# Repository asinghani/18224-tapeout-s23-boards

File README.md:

# 18-224 S23 Tapeout Bringup

## Getting Started

If you have picked up your kit from ECE, please see [BRINGUP.md](docs/BRINGUP.md) for instructions on how to get started using it!

If you are interested in the process to assemble the boards/kits, see [ASSEMBLY.md](docs/ASSEMBLY.md)

## Schematics

- Breakout Board v1 [Schematic](pcb/breakout_board_v1/schematic.pdf)
- Buttons/Switches Board [Schematic](pcb/manual_gpio_board/schematic.pdf)
- Debugger Board [Schematic](pcb/debugger_board_v1/schematic.pdf)

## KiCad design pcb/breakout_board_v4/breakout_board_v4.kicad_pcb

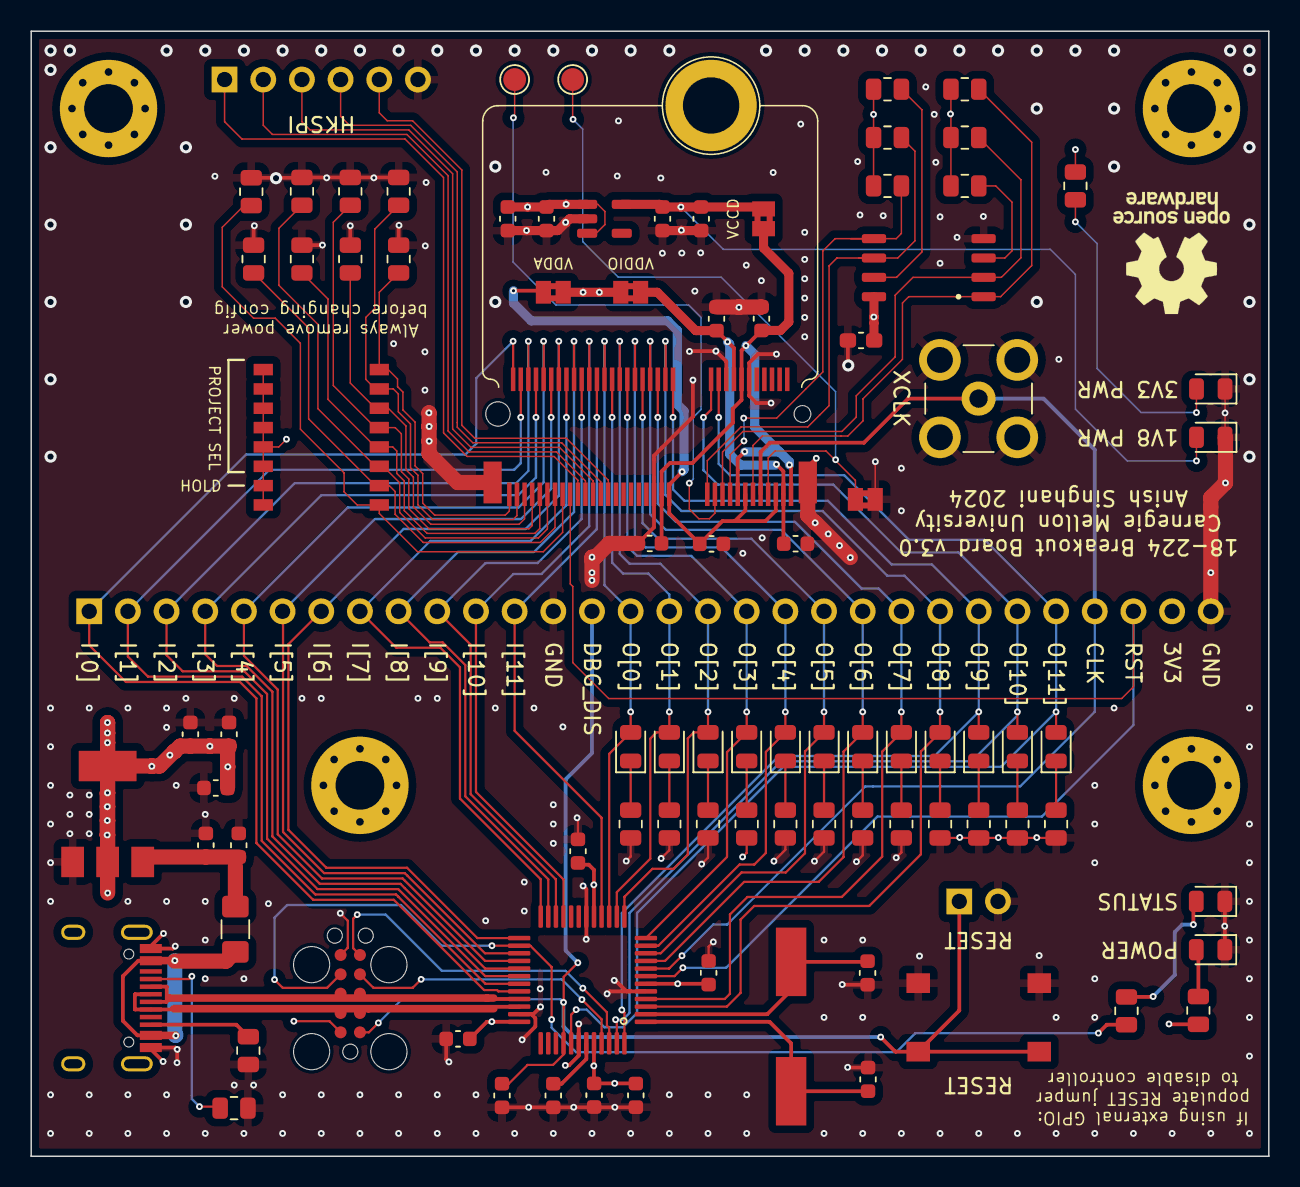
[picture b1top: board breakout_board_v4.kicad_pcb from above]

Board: 4 copper layers, 81.3 x 73.9 mm, 97 parts (0 on the bottom side), 81 nets.

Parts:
C1, C2: 22p; C_0603_1608Metric
C3, C5, C7, C8, C9, C12, C13, C20: 0.1u; C_0603_1608Metric
C4, C6, C11, C14, C15, C19, C21, C24: 1u; C_0603_1608Metric
C10, C16, C18, C22, C23: 10u; C_0603_1608Metric
C17: DNF; C_0603_1608Metric_Pad1.08x0.95mm_HandSolder
D1: 3V3; LED_0805_2012Metric
D2, D3, D4, D6, D7, D8, D9, D10, D11, D12, D13, D14, D15, D16: LED; LED_0805_2012Metric
D5: 1V8; LED_0805_2012Metric
F1: 500mA; Fuse_1206_3216Metric_Pad1.42x1.75mm_HandSolder
H1: MICROMOD-Standoff; MicroMod-Standoff
H2, H3, H4, H5: MountingHole; MountingHole_3.2mm_M3_Pad_Via
J1: TC2050; Tag-Connect_TC2050-IDC-FP_2x05_P1.27mm_Vertical
J2: SMA_CONN; SMB_Jack_Vertical
J3: BREAKOUT_HDR; PinHeader_1x30_P2.54mm_Vertical
J4: HKSPI_HDR; PinHeader_1x06_P2.54mm_Vertical
J5: USB_C_Receptacle_USB2.0; USB_C_Receptacle_HRO_TYPE-C-31-M-12
JP1: RST_JMP; PinHeader_1x02_P2.54mm_Vertical
JP2: VCCD_JMP; SolderJumper-2_P1.3mm_Bridged2Bar_Pad1.0x1.5mm
JP3: VDDA_JMP; SolderJumper-2_P1.3mm_Bridged2Bar_Pad1.0x1.5mm
JP4: SOC_RST_JMP; SolderJumper-2_P1.3mm_Bridged2Bar_Pad1.0x1.5mm
JP5: VDDIO_JMP; SolderJumper-2_P1.3mm_Bridged2Bar_Pad1.0x1.5mm
R1, R2, R3, R4, R5, R6, R7, R8, R12: 10K; R_0805_2012Metric
R9, R10, R11, R13, R14: DNF; R_0805_2012Metric
R15, R16, R17, R18, R19, R20, R21, R22, R23, R24, R25, R26, R27, R28, R29: 1K; R_0805_2012Metric
R30, R31: 5.1K; R_0805_2012Metric
SW1: RST_BTN; SW_Push_1P1T_NO_6x6mm_H9.5mm
SW2: DSHP08TSGER; SW_DIP_SPSTx08_Slide_KingTek_DSHP08TS_W7.62mm_P1.27mm
TP1: CARAVEL_GPIO_TP; TestPoint_Pad_D1.5mm
TP2: RST_TP; TestPoint_Pad_D1.5mm
U1: ATSAMD21G18A-A; TQFP-48_7x7mm_P0.5mm
U2: caravel-M.2-card; M.2-CONNECTOR-E
U3: AP2112K-1.8; SOT-23-5
U4: DNF; SOIC-8_5.23x5.23mm_P1.27mm
U5: AZ1117-3.3; SOT-223-3_TabPin2
Y1: 32.768KHz; Crystal_SMD_HC49-SD

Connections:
+1V8: C14.1, C16.1, D5.2 (A), JP2.2 (B), U3.5 (VOUT)
+3V3: C4.1, C5.1, C7.1, C8.1, C9.1, C10.1, C12.1, C17.1, C22.1, C23.1, C24.1, J1.10, J3.29, JP3.2 (B), JP5.2 (B), R9.1, R10.1, R11.1, R12.1, R13.1, R14.1, R15.2, R21.1, SW2.1, SW2.2, SW2.3, SW2.4, SW2.5, SW2.6, SW2.7, SW2.8, U1.6 (VDDANA), U1.17 (VDDIO), U1.36 (VDDIO), U1.44 (VDDIN), U3.1 (VIN), U3.3 (EN), U4.8 (VCC), U5.2 (VO)
+5V: C18.1, C21.1, F1.1, U5.3 (VI)
Caravel_CSB: R9.2, U2.11 (Caravel_CSB), U4.1 (~CS)
Caravel_D0: R11.2, U2.17 (Caravel_D0), U4.5 (DI(IO0))
Caravel_D1: R12.2, U2.19 (Caravel_D1), U4.2 (DO(IO1))
Caravel_SCK: R10.2, U2.23 (Caravel_SCK), U4.6 (CLK)
Flash_HOLD: R14.2, U4.7 (IO3)
Flash_WP: R13.2, U4.3 (IO2)
GND: C1.1, C2.1, C3.2, C4.2, C5.2, C6.1, C7.2, C8.2, C9.2, C10.2, C11.2, C12.2, C13.2, C14.2, C15.2, C16.2, C17.2, C18.2, C19.2, C20.2, C21.2, C22.2, C23.2, C24.2, D1.1 (K), D4.1 (K), D5.1 (K), D8.1 (K), J1.6, J2.2 (Ext), J3.13, J3.30, J4.6, J5.A1 (GND), J5.A12 (GND), J5.B1 (GND), J5.B12 (GND), JP1.2 (B), JP4.2 (B), R1.2, R2.2, R3.2, R4.2, R5.2, R6.2, R7.2, R8.2, R16.2, R17.2, R19.2, R20.2, R22.2, R23.2, R24.2, R25.2, R26.2, R27.2, R28.2, R29.2, R30.1, R31.1, SW1.1, U1.5 (GNDANA), U1.18 (GND), U1.35 (GND), U1.42 (GND), U2.12 (GND), U2.18 (GND), U2.37 (GND), U2.A1 (GND), U2.A2 (GND), U3.2 (GND), U4.4 (GND), U5.1 (GND)
unnamed: D1.2 (A), R15.1
unnamed: D2.1 (K), R16.1
unnamed: D3.1 (K), R17.1
unnamed: D4.2 (A), R18.2
unnamed: D6.1 (K), R19.1
unnamed: D7.1 (K), R20.1
unnamed: D8.2 (A), R21.2
unnamed: D9.1 (K), R22.1
unnamed: D10.1 (K), R23.1
unnamed: D11.1 (K), R24.1
unnamed: D12.1 (K), R25.1
unnamed: D13.1 (K), R26.1
unnamed: D14.1 (K), R27.1
unnamed: D15.1 (K), R28.1
unnamed: D16.1 (K), R29.1
unnamed: F1.2, J5.A4 (VBUS), J5.A9 (VBUS), J5.B4 (VBUS), J5.B9 (VBUS)
unnamed: J5.A5 (CC1), R30.2
unnamed: J5.B5 (CC2), R31.2
unnamed: C1.2, U1.1 (PA00), Y1.1
unnamed: C2.2, U1.2 (PA01), Y1.2
unnamed: C6.2, U1.43 (VDDCORE)
RESETn: C3.1, J1.1, J3.14, JP1.1 (A), SW1.2, U1.40 (~RESET)
SWC: J1.4, U1.45 (PA30)
SWD: J1.5, U1.46 (PA31)
USB_DM: J1.3, J1.8, J5.A7 (D-), J5.B7 (D-), U1.33 (PA24)
USB_DP: J1.2, J1.9, J5.A6 (D+), J5.B6 (D+), U1.34 (PA25)
gpio: TP1.1, U2.21 (gpio)
in0: J3.1, U1.32 (PA23), U2.74 (mprj_io[14])
in1: J3.2, U1.31 (PA22), U2.72 (mprj_io[15])
in2: J3.3, U1.30 (PA21), U2.70 (mprj_io[16])
in3: J3.4, U1.29 (PA20), U2.68 (mprj_io[17])
in4: J3.5, U1.28 (PA19), U2.66 (mprj_io[18])
in5: J3.6, U1.27 (PA18), U2.64 (mprj_io[19])
in6: J3.7, U1.25 (PA16), U2.62 (mprj_io[20])
in7: J3.8, U1.24 (PA15), U2.60 (mprj_io[21])
in8: J3.9, U1.23 (PA14), U2.58 (mprj_io[22])
in9: J3.10, U1.22 (PA13), U2.56 (mprj_io[23])
in10: J3.11, U1.21 (PA12), U2.54 (mprj_io[24])
in11: J3.12, U1.16 (PA11), U2.52 (mprj_io[25])
mprj_io[0]: J4.5, U2.49 (mprj_io[0])
mprj_io[1]_SDO: J4.4, U2.51 (mprj_io[1]_SDO)
mprj_io[2]_SDI: J4.3, U2.53 (mprj_io[2]_SDI)
mprj_io[3]_CSB: J4.2, U2.55 (mprj_io[3]_CSB)
mprj_io[4]_SCK: J4.1, U2.57 (mprj_io[4]_SCK)
mprj_io[5]_ser_rx: J3.28, U1.7 (PB08), U2.59 (mprj_io[5]_ser_rx)
mprj_io[6]_ser_tx: R1.1, SW2.9, U2.61 (mprj_io[6]_ser_tx)
mprj_io[7]: R2.1, SW2.10, U2.63 (mprj_io[7])
mprj_io[8]: R3.1, SW2.11, U2.65 (mprj_io[8])
mprj_io[9]: R4.1, SW2.12, U2.67 (mprj_io[9])
mprj_io[10]: R5.1, SW2.13, U2.69 (mprj_io[10])
mprj_io[11]: R6.1, SW2.14, U2.71 (mprj_io[11])
mprj_io[12]: R7.1, SW2.15, U2.73 (mprj_io[12])
mprj_io[13]: R8.1, SW2.16, U2.75 (mprj_io[13])
mprj_io[26]: D2.2 (A), J3.15, U1.15 (PA10), U2.50 (mprj_io[26])
mprj_io[27]: D6.2 (A), J3.16, U1.14 (PA09), U2.48 (mprj_io[27])
mprj_io[28]: D9.2 (A), J3.17, U1.13 (PA08), U2.46 (mprj_io[28])
mprj_io[29]: D11.2 (A), J3.18, U1.12 (PA07), U2.44 (mprj_io[29])
mprj_io[30]: D13.2 (A), J3.19, U1.11 (PA06), U2.42 (mprj_io[30])
mprj_io[31]: D15.2 (A), J3.20, U1.10 (PA05), U2.40 (mprj_io[31])
mprj_io[32]: D3.2 (A), J3.21, U1.9 (PA04), U2.38 (mprj_io[32])
mprj_io[33]: D7.2 (A), J3.22, U1.4 (PA03), U2.36 (mprj_io[33])
mprj_io[34]: D10.2 (A), J3.23, U1.3 (PA02), U2.34 (mprj_io[34])
mprj_io[35]: D12.2 (A), J3.24, U1.48 (PB03), U2.32 (mprj_io[35])
mprj_io[36]: D14.2 (A), J3.25, U1.47 (PB02), U2.22 (mprj_io[36])
mprj_io[37]: D16.2 (A), J3.26, U1.41 (PA28), U2.20 (mprj_io[37])
status: J1.7, R18.1, U1.26 (PA17)
uio_clk: J2.1 (In), J3.27, U1.8 (PB09), U2.9 (xclk)
vccd: C11.1, C13.1, JP2.1 (A), U2.1 (vccd2), U2.14 (vccd), U2.15 (vcdd), U2.35 (vccd1)
vdda: C15.1, JP3.1 (A), U2.5 (vdda), U2.13 (vdda2), U2.33 (vdda1)
vddio: C19.1, C20.1, JP5.1 (A), U2.3 (vddio), U2.16 (vddio)
~RST: JP4.1 (A), TP2.1, U2.7 (~RST)

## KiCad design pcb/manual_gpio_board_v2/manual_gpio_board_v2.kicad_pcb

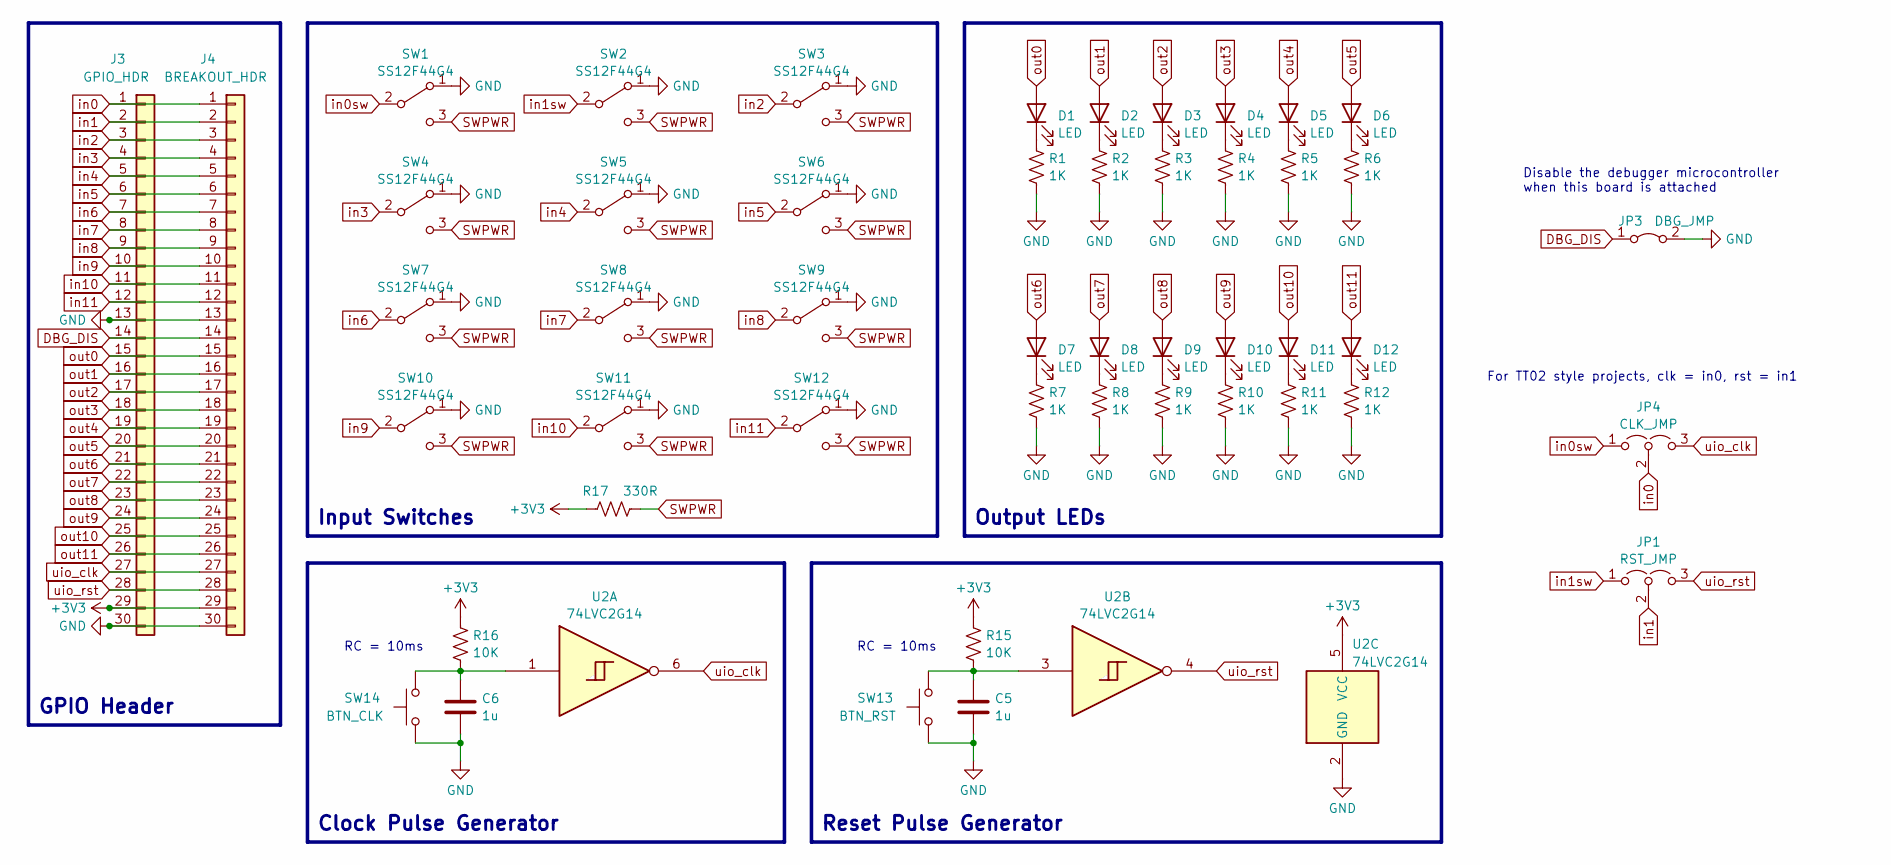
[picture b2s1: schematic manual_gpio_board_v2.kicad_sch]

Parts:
C5, C6: 1u; C_0603_1608Metric; LCSC C15849
D1, D2, D3, D4, D5, D6, D7, D8, D9, D10, D11, D12: LED; LED_0805_2012Metric; LCSC C98221
J3: GPIO_HDR; PinHeader_1x30_P2.54mm_Vertical
J4: BREAKOUT_HDR; PinHeader_1x30_P2.54mm_Vertical
JP1: RST_JMP; PinHeader_1x03_P2.54mm_Vertical
JP3: DBG_JMP; SolderJumper-2_P1.3mm_Bridged_Pad1.0x1.5mm
JP4: CLK_JMP; PinHeader_1x03_P2.54mm_Vertical
R1, R2, R3, R4, R5, R6, R7, R8, R9, R10, R11, R12: 1K; R_0805_2012Metric; LCSC C17513
R15, R16: 10K; R_0805_2012Metric; LCSC C17414
R17: 330R; R_0805_2012Metric; LCSC C17630
SW1, SW2, SW3, SW4, SW5, SW6, SW7, SW8, SW9, SW10, SW11, SW12: SS12F44G4
SW13: BTN_RST; SW_Push_1P1T_NO_6x6mm_H9.5mm; LCSC C294566
SW14: BTN_CLK; SW_Push_1P1T_NO_6x6mm_H9.5mm; LCSC C294566
U2: 74LVC2G14; SOT-23-6; LCSC C12401

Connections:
+3V3: J3.29, R15.1, R16.1, R17.1, U2.5 (VCC); also elsewhere on the board
DBG_DIS: J3.14, JP3.1 (A); also elsewhere on the board
GND: C5.2, C6.2, J3.13, J3.30, JP3.2 (B), R1.2, R2.2, R3.2, R4.2, R5.2, R6.2, R7.2, R8.2, R9.2, R10.2, R11.2, R12.2, SW1.1 (A), SW2.1 (A), SW3.1 (A), SW4.1 (A), SW5.1 (A), SW6.1 (A), SW7.1 (A), SW8.1 (A), SW9.1 (A), SW10.1 (A), SW11.1 (A), SW12.1 (A), SW13.1, SW14.1, U2.2 (GND); also elsewhere on the board
unnamed: C5.1, R15.2, SW13.2, U2.3
unnamed: C6.1, R16.2, SW14.2, U2.1
unnamed: D1.1 (K), R1.1
unnamed: D2.1 (K), R2.1
unnamed: D3.1 (K), R3.1
unnamed: D4.1 (K), R4.1
unnamed: D5.1 (K), R5.1
unnamed: D6.1 (K), R6.1
unnamed: D7.1 (K), R7.1
unnamed: D8.1 (K), R8.1
unnamed: D9.1 (K), R9.1
unnamed: D10.1 (K), R10.1
unnamed: D11.1 (K), R11.1
unnamed: D12.1 (K), R12.1
SWPWR: R17.2, SW1.3 (C), SW2.3 (C), SW3.3 (C), SW4.3 (C), SW5.3 (C), SW6.3 (C), SW7.3 (C), SW8.3 (C), SW9.3 (C), SW10.3 (C), SW11.3 (C), SW12.3 (C)
in0: J3.1, JP4.2 (C); also elsewhere on the board
in0sw: JP4.1 (A), SW1.2 (B)
in1: J3.2, JP1.2 (C); also elsewhere on the board
in1sw: JP1.1 (A), SW2.2 (B)
in2: J3.3, SW3.2 (B); also elsewhere on the board
in3: J3.4, SW4.2 (B); also elsewhere on the board
in4: J3.5, SW5.2 (B); also elsewhere on the board
in5: J3.6, SW6.2 (B); also elsewhere on the board
in6: J3.7, SW7.2 (B); also elsewhere on the board
in7: J3.8, SW8.2 (B); also elsewhere on the board
in8: J3.9, SW9.2 (B); also elsewhere on the board
in9: J3.10, SW10.2 (B); also elsewhere on the board
in10: J3.11, SW11.2 (B); also elsewhere on the board
in11: J3.12, SW12.2 (B); also elsewhere on the board
out0: D1.2 (A), J3.15; also elsewhere on the board
out1: D2.2 (A), J3.16; also elsewhere on the board
out2: D3.2 (A), J3.17; also elsewhere on the board
out3: D4.2 (A), J3.18; also elsewhere on the board
out4: D5.2 (A), J3.19; also elsewhere on the board
out5: D6.2 (A), J3.20; also elsewhere on the board
out6: D7.2 (A), J3.21; also elsewhere on the board
out7: D8.2 (A), J3.22; also elsewhere on the board
out8: D9.2 (A), J3.23; also elsewhere on the board
out9: D10.2 (A), J3.24; also elsewhere on the board
out10: D11.2 (A), J3.25; also elsewhere on the board
out11: D12.2 (A), J3.26; also elsewhere on the board
uio_clk: J3.27, JP4.3 (B), U2.6; also elsewhere on the board
uio_rst: J3.28, JP1.3 (B), U2.4; also elsewhere on the board

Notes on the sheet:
For TT02 style projects, clk = in0, rst = in1
RC = 10ms
Disable the debugger microcontroller when this board is attached
Input Switches
Reset Pulse Generator
Clock Pulse Generator
GPIO Header
Output LEDs

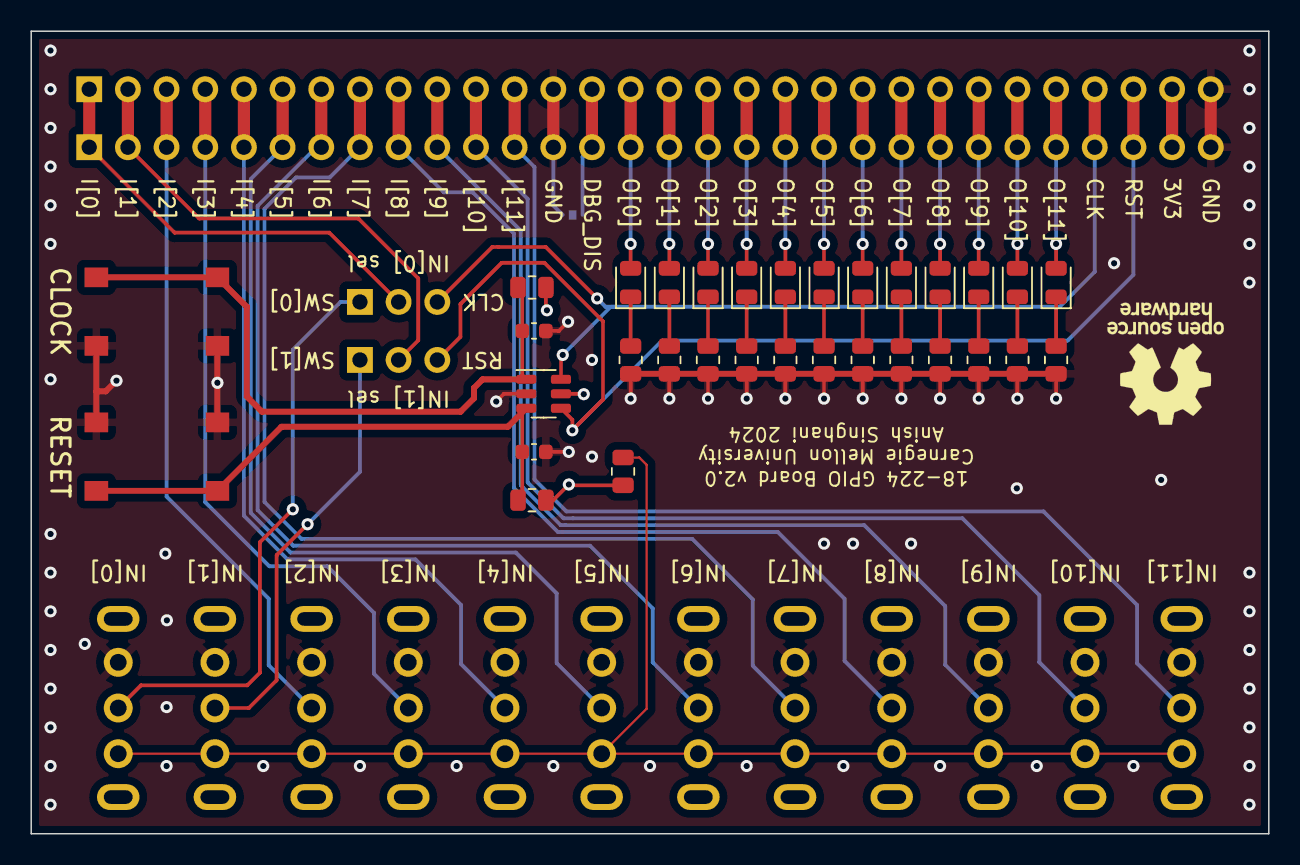
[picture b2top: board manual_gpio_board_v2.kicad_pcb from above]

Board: 4 copper layers, 81.3 x 52.7 mm, 49 parts (1 on the bottom side), 46 nets.

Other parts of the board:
J1: GPIO_HDR; PinHeader_1x30_P2.54mm_Vertical

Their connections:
+3V3: J1.29; also elsewhere on the board
DBG_DIS: J1.14; also elsewhere on the board
GND: J1.13, J1.30; also elsewhere on the board
in0: J1.1; also elsewhere on the board
in1: J1.2; also elsewhere on the board
in2: J1.3; also elsewhere on the board
in3: J1.4; also elsewhere on the board
in4: J1.5; also elsewhere on the board
in5: J1.6; also elsewhere on the board
in6: J1.7; also elsewhere on the board
in7: J1.8; also elsewhere on the board
in8: J1.9; also elsewhere on the board
in9: J1.10; also elsewhere on the board
in10: J1.11; also elsewhere on the board
in11: J1.12; also elsewhere on the board
out0: J1.15; also elsewhere on the board
out1: J1.16; also elsewhere on the board
out2: J1.17; also elsewhere on the board
out3: J1.18; also elsewhere on the board
out4: J1.19; also elsewhere on the board
out5: J1.20; also elsewhere on the board
out6: J1.21; also elsewhere on the board
out7: J1.22; also elsewhere on the board
out8: J1.23; also elsewhere on the board
out9: J1.24; also elsewhere on the board
out10: J1.25; also elsewhere on the board
out11: J1.26; also elsewhere on the board
uio_clk: J1.27; also elsewhere on the board
uio_rst: J1.28; also elsewhere on the board

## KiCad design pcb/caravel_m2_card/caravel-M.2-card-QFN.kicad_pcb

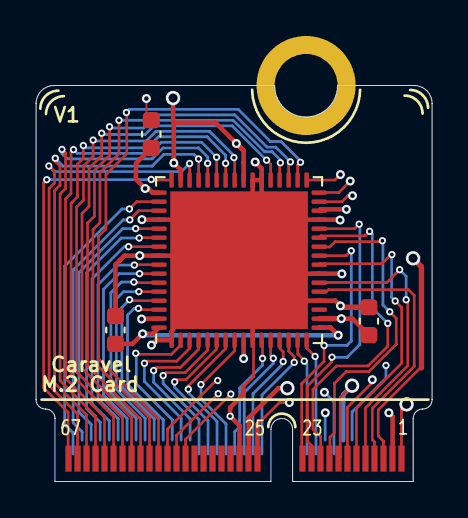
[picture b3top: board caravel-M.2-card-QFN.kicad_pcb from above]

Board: 4 copper layers, 22.0 x 22.0 mm, 5 parts (0 on the bottom side), 53 nets.

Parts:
C1, C4, C6: 0.1uf; C_0603_1608Metric
J1: MICROMOD-2222-Generic; MicroMod-M.2-CARD-E-22
U1: Caravel; QFN-64-1EP_9x9mm_P0.5mm_EP7.65x7.65mm

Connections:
Caravel_CSB: J1.11, U1.24 (flash_csb)
Caravel_D0: J1.17, U1.26 (flash_io0)
Caravel_D1: J1.19, U1.27 (flash_io1)
Caravel_SCK: J1.23, U1.25 (flash_clk)
GND: C1.1, C4.1, C6.1, J1.12, J1.18, J1.37 (P29), J1.GND, U1.1 (vssa2), U1.10 (vssd2), U1.20 (vssa), U1.23 (vssd), U1.29 (vssio), U1.38 (vssa1), U1.39 (vssd1), U1.52 (vssa1), U1.56 (vssio), U1.65 (ThermalPad)
gpio: J1.21, U1.28 (gpio)
mprj_io[0]: J1.49 (P41), U1.31 (mprj_io[0]_JTAG)
mprj_io[1]_SDO: J1.51 (P43), U1.32 (mprj_io[1]_SDO)
mprj_io[2]_SDI: J1.53 (P45), U1.33 (mprj_io[2]_SDI)
mprj_io[3]_CSB: J1.55 (P47), U1.34 (mprj_io[3]_CSB)
mprj_io[4]_SCK: J1.57 (P49), U1.35 (mprj_io[4]_SCK)
mprj_io[5]_ser_rx: J1.59 (P51), U1.36 (mprj_io[5]_ser_rx)
mprj_io[6]_ser_tx: J1.61 (P53), U1.37 (mprj_io[6]_ser_tx)
mprj_io[7]: J1.63 (P55), U1.41 (mprj_io[7])
mprj_io[8]: J1.65 (P57), U1.42 (mprj_io[8])
mprj_io[9]: J1.67 (P59), U1.43 (mprj_io[9])
mprj_io[10]: J1.69 (P61), U1.44 (mprj_io[10])
mprj_io[11]: J1.71 (P63), U1.45 (mprj_io[11])
mprj_io[12]: J1.73 (P65), U1.46 (mprj_io[12])
mprj_io[13]: J1.75 (P67), U1.48 (mprj_io[13])
mprj_io[14]: J1.74 (P66), U1.50 (mprj_io[14])
mprj_io[15]: J1.72 (P64), U1.51 (mprj_io[15])
mprj_io[16]: J1.70 (P62), U1.53 (mprj_io[16])
mprj_io[17]: J1.68 (P60), U1.54 (mprj_io[17])
mprj_io[18]: J1.66 (P58), U1.55 (mprj_io[18])
mprj_io[19]: J1.64 (P56), U1.57 (mprj_io[19])
mprj_io[20]: J1.62 (P54), U1.58 (mprj_io[20])
mprj_io[21]: J1.60 (P52), U1.59 (mprj_io[21])
mprj_io[22]: J1.58 (P50), U1.60 (mprj_io[22])
mprj_io[23]: J1.56 (P48), U1.61 (mprj_io[23])
mprj_io[24]: J1.54 (P46), U1.62 (mprj_io[24])
mprj_io[25]: J1.52 (P44), U1.2 (mprj_io[25])
mprj_io[26]: J1.50 (P42), U1.3 (mprj_io[26])
mprj_io[27]: J1.48 (P40), U1.4 (mprj_io[27])
mprj_io[28]: J1.46 (P38), U1.5 (mprj_io[28])
mprj_io[29]: J1.44 (P36), U1.6 (mprj_io[29])
mprj_io[30]: J1.42 (P34), U1.7 (mprj_io[30])
mprj_io[31]: J1.40 (P32), U1.8 (mprj_io[31])
mprj_io[32]: J1.38 (P30), U1.11 (mprj_io[32])
mprj_io[33]: J1.36 (P28), U1.12 (mprj_io[33])
mprj_io[34]: J1.34 (P26), U1.13 (mprj_io[34])
mprj_io[35]: J1.32 (P24), U1.14 (mprj_io[35])
mprj_io[36]: J1.22, U1.15 (mprj_io[36])
mprj_io[37]: J1.20, U1.16 (mprj_io[37])
vccd: C4.2, J1.14, J1.15, U1.18 (vccd)
vccd1: C1.2, J1.35 (P27), U1.49 (vccd1)
vccd2: J1.1, U1.63 (vccd2)
vdda: J1.5, U1.30 (vdda)
vdda1: J1.33 (P25), U1.40 (vdda1), U1.47 (vdda1)
vdda2: J1.13, U1.9 (vdda2)
vddio: C6.2, J1.3, J1.16, U1.17 (vddio), U1.64 (vddio)
xclk: J1.9, U1.22 (clock)
~RST: J1.7, U1.21 (resetb)

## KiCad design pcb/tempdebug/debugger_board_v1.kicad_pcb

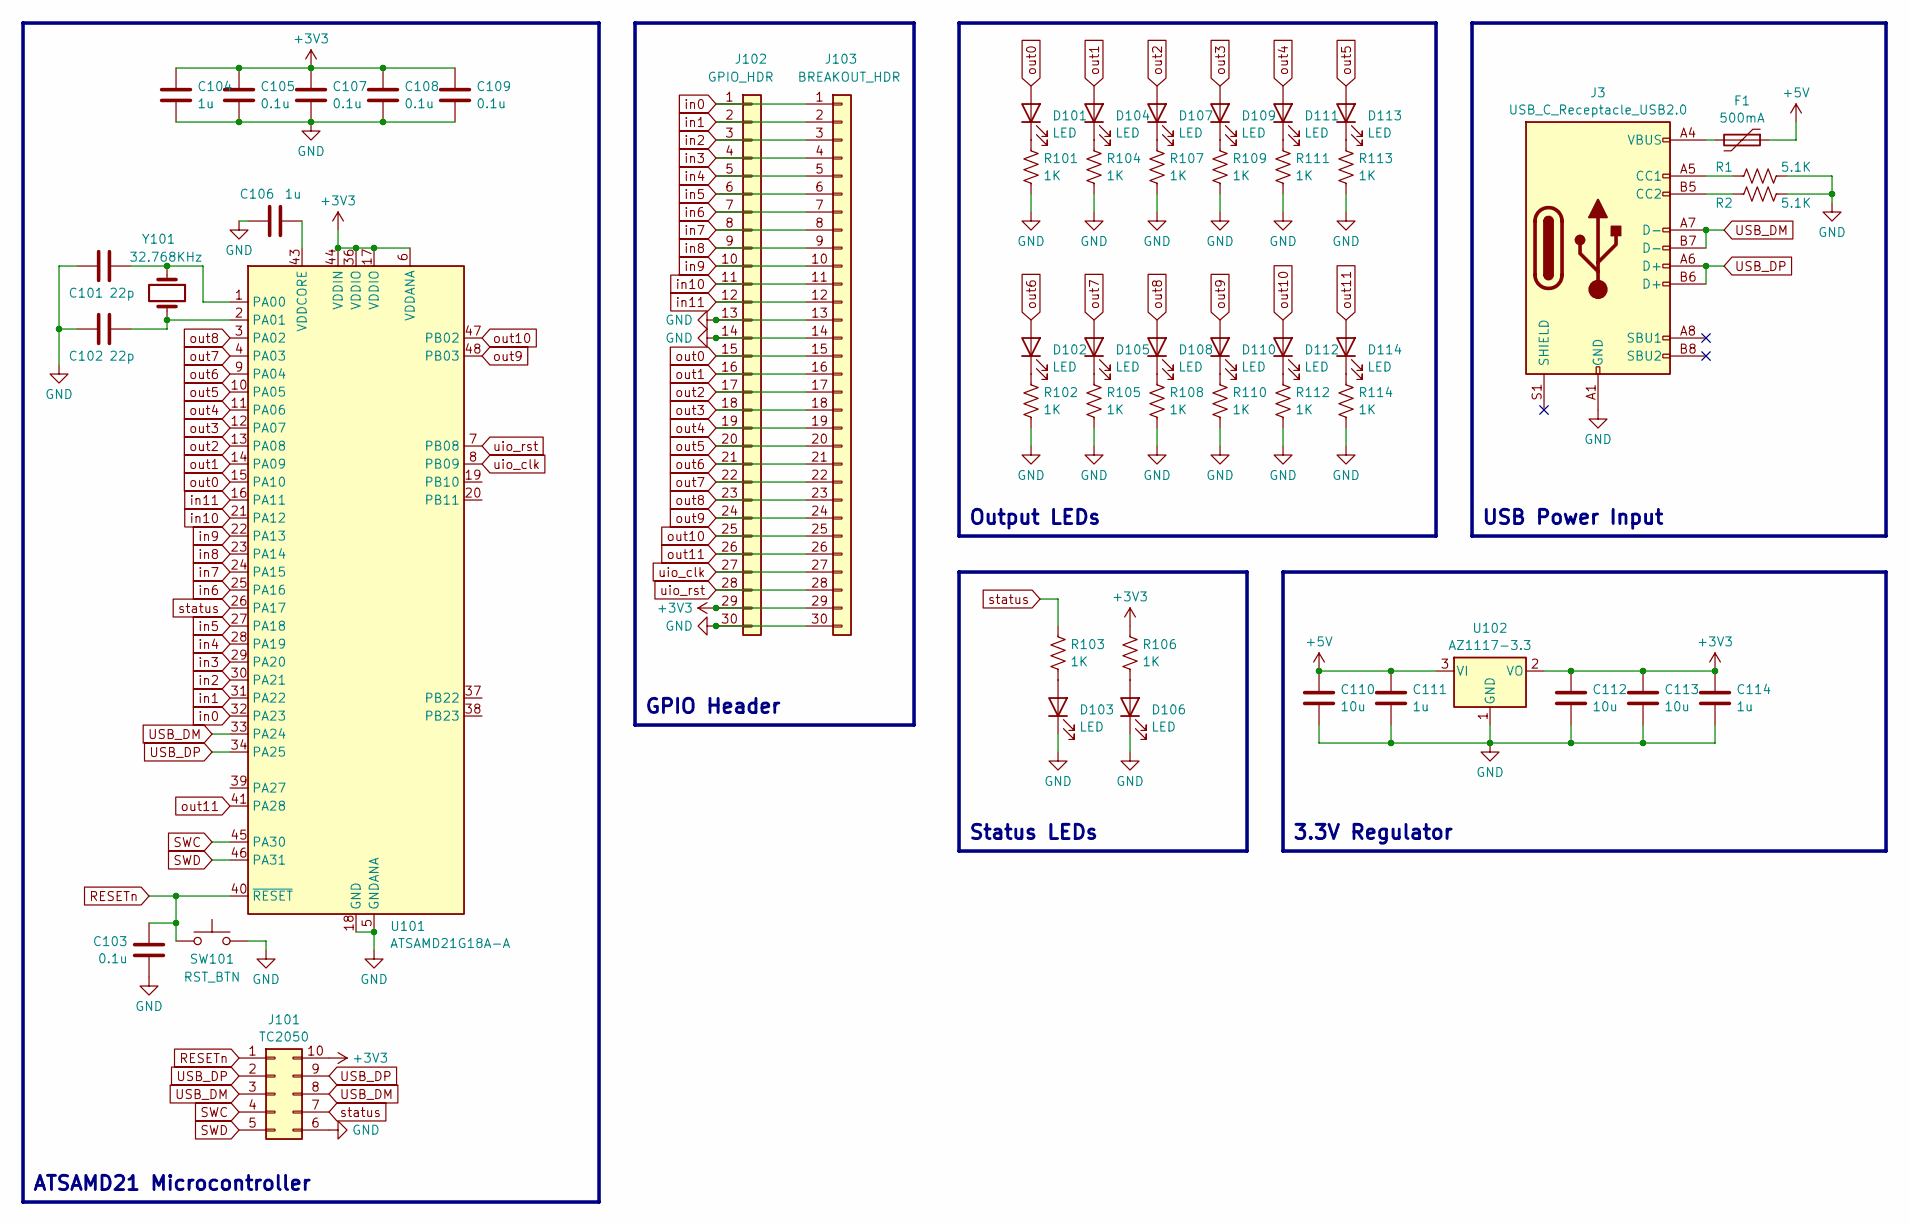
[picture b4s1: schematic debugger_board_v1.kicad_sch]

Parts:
C101, C102: 22p; C_0603_1608Metric; LCSC C1653
C103, C105, C107, C108, C109: 0.1u; C_0603_1608Metric; LCSC C14663
C104, C106, C111, C114: 1u; C_0603_1608Metric; LCSC C15849
C110, C112, C113: 10u; C_0603_1608Metric; LCSC C19702
D101, D102, D103, D104, D105, D106, D107, D108, D109, D110, D111, D112, D113, D114: LED; LED_0805_2012Metric; LCSC C98221
F1: 500mA; Fuse_1206_3216Metric_Pad1.42x1.75mm_HandSolder
J3: USB_C_Receptacle_USB2.0; USB_C_Receptacle_HRO_TYPE-C-31-M-12; LCSC C165948
J101: TC2050; Tag-Connect_TC2050-IDC-FP_2x05_P1.27mm_Vertical
J102: GPIO_HDR; PinHeader_1x30_P2.54mm_Vertical
J103: BREAKOUT_HDR; PinHeader_1x30_P2.54mm_Vertical
R1, R2: 5.1K; R_0805_2012Metric; LCSC C17513
R101, R102, R103, R104, R105, R106, R107, R108, R109, R110, R111, R112, R113, R114: 1K; R_0805_2012Metric; LCSC C17513
SW101: RST_BTN; SW_Push_1P1T_NO_6x6mm_H9.5mm; LCSC C294566
U101: ATSAMD21G18A-A; TQFP-48_7x7mm_P0.5mm; LCSC C78624
U102: AZ1117-3.3; SOT-223-3_TabPin2; LCSC C92102
Y101: 32.768KHz; Crystal_SMD_HC49-SD; LCSC C2838414

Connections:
+3V3: C104.1, C105.1, C107.1, C108.1, C109.1, C112.1, C113.1, C114.1, J101.10, J102.29, J103.29, R106.1, U101.6 (VDDANA), U101.17 (VDDIO), U101.36 (VDDIO), U101.44 (VDDIN), U102.2 (VO)
+5V: C110.1, C111.1, U102.3 (VI); also elsewhere on the board
GND: C101.1, C102.1, C103.2, C104.2, C105.2, C106.1, C107.2, C108.2, C109.2, C110.2, C111.2, C112.2, C113.2, C114.2, D103.1 (K), D106.1 (K), J101.6, J102.13, J102.14, J102.30, J103.13, J103.14, J103.30, R101.2, R102.2, R104.2, R105.2, R107.2, R108.2, R109.2, R110.2, R111.2, R112.2, R113.2, R114.2, SW101.1, U101.5 (GNDANA), U101.18 (GND), U101.35 (GND), U101.42 (GND), U102.1 (GND); also elsewhere on the board
unnamed: D101.1 (K), R101.1
unnamed: D102.1 (K), R102.1
unnamed: D103.2 (A), R103.2
unnamed: D104.1 (K), R104.1
unnamed: D105.1 (K), R105.1
unnamed: D106.2 (A), R106.2
unnamed: D107.1 (K), R107.1
unnamed: D108.1 (K), R108.1
unnamed: D109.1 (K), R109.1
unnamed: D110.1 (K), R110.1
unnamed: D111.1 (K), R111.1
unnamed: D112.1 (K), R112.1
unnamed: D113.1 (K), R113.1
unnamed: D114.1 (K), R114.1
unnamed: C101.2, U101.1 (PA00), Y101.1
unnamed: C102.2, U101.2 (PA01), Y101.2
unnamed: C106.2, U101.43 (VDDCORE)
RESETn: C103.1, J101.1, SW101.2, U101.40 (~RESET)
SWC: J101.4, U101.45 (PA30)
SWD: J101.5, U101.46 (PA31)
USB_DM: J101.3, J101.8, U101.33 (PA24); also elsewhere on the board
USB_DP: J101.2, J101.9, U101.34 (PA25); also elsewhere on the board
in0: J102.1, J103.1, U101.32 (PA23)
in1: J102.2, J103.2, U101.31 (PA22)
in2: J102.3, J103.3, U101.30 (PA21)
in3: J102.4, J103.4, U101.29 (PA20)
in4: J102.5, J103.5, U101.28 (PA19)
in5: J102.6, J103.6, U101.27 (PA18)
in6: J102.7, J103.7, U101.25 (PA16)
in7: J102.8, J103.8, U101.24 (PA15)
in8: J102.9, J103.9, U101.23 (PA14)
in9: J102.10, J103.10, U101.22 (PA13)
in10: J102.11, J103.11, U101.21 (PA12)
in11: J102.12, J103.12, U101.16 (PA11)
out0: D101.2 (A), J102.15, J103.15, U101.15 (PA10)
out1: D104.2 (A), J102.16, J103.16, U101.14 (PA09)
out2: D107.2 (A), J102.17, J103.17, U101.13 (PA08)
out3: D109.2 (A), J102.18, J103.18, U101.12 (PA07)
out4: D111.2 (A), J102.19, J103.19, U101.11 (PA06)
out5: D113.2 (A), J102.20, J103.20, U101.10 (PA05)
out6: D102.2 (A), J102.21, J103.21, U101.9 (PA04)
out7: D105.2 (A), J102.22, J103.22, U101.4 (PA03)
out8: D108.2 (A), J102.23, J103.23, U101.3 (PA02)
out9: D110.2 (A), J102.24, J103.24, U101.48 (PB03)
out10: D112.2 (A), J102.25, J103.25, U101.47 (PB02)
out11: D114.2 (A), J102.26, J103.26, U101.41 (PA28)
status: J101.7, R103.1, U101.26 (PA17)
uio_clk: J102.27, J103.27, U101.8 (PB09)
uio_rst: J102.28, J103.28, U101.7 (PB08)

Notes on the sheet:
3.3V Regulator
Status LEDs
Output LEDs
USB Power Input
ATSAMD21 Microcontroller
GPIO Header

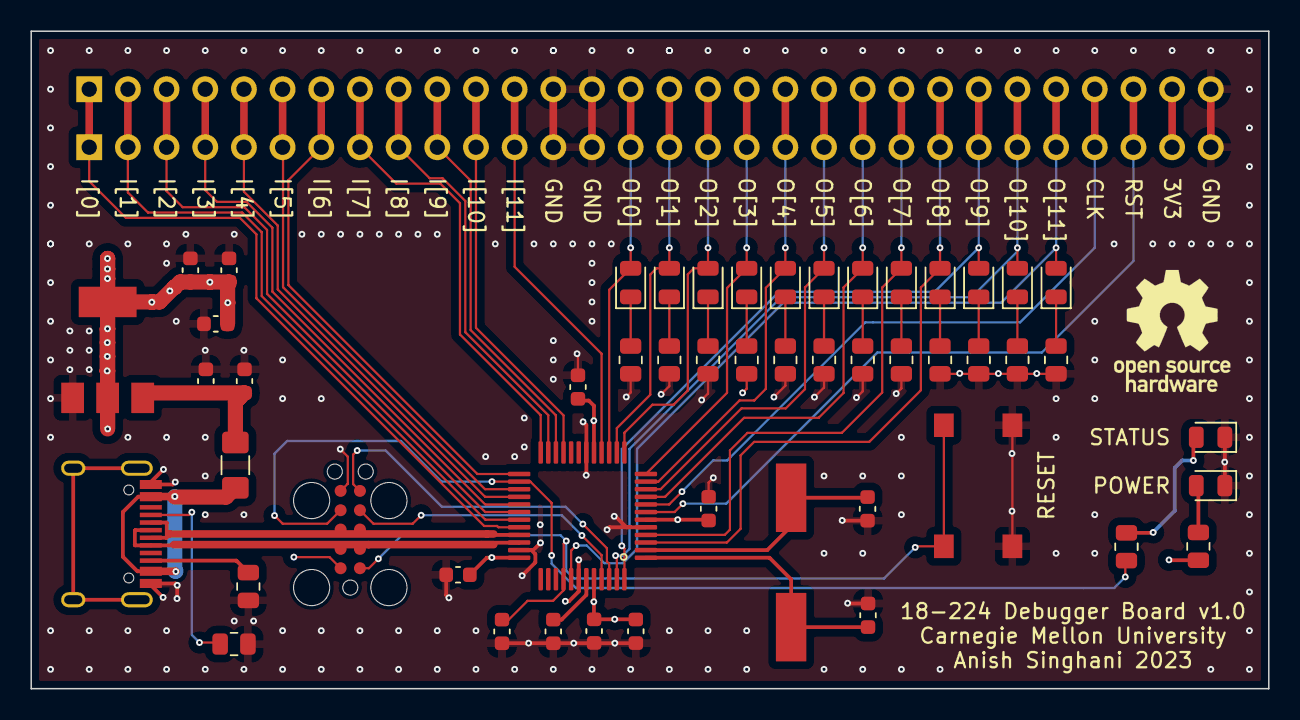
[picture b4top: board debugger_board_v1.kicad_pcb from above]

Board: 4 copper layers, 81.3 x 43.2 mm, 53 parts (0 on the bottom side), 55 nets.

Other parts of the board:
F101: 500mA; Fuse_1206_3216Metric_Pad1.42x1.75mm_HandSolder
J104: USB_C_Receptacle_USB2.0; USB_C_Receptacle_HRO_TYPE-C-31-M-12
R115, R116: 5.1K; R_0805_2012Metric

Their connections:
+5V: F101.1; also elsewhere on the board
GND: J104.A1 (GND), J104.A12 (GND), J104.B1 (GND), J104.B12 (GND), R115.1, R116.1; also elsewhere on the board
unnamed: F101.2, J104.A4 (VBUS), J104.A9 (VBUS), J104.B4 (VBUS), J104.B9 (VBUS)
unnamed: J104.A5 (CC1), R115.2
unnamed: J104.B5 (CC2), R116.2
USB_DM: J104.A7 (D-), J104.B7 (D-); also elsewhere on the board
USB_DP: J104.A6 (D+), J104.B6 (D+); also elsewhere on the board
